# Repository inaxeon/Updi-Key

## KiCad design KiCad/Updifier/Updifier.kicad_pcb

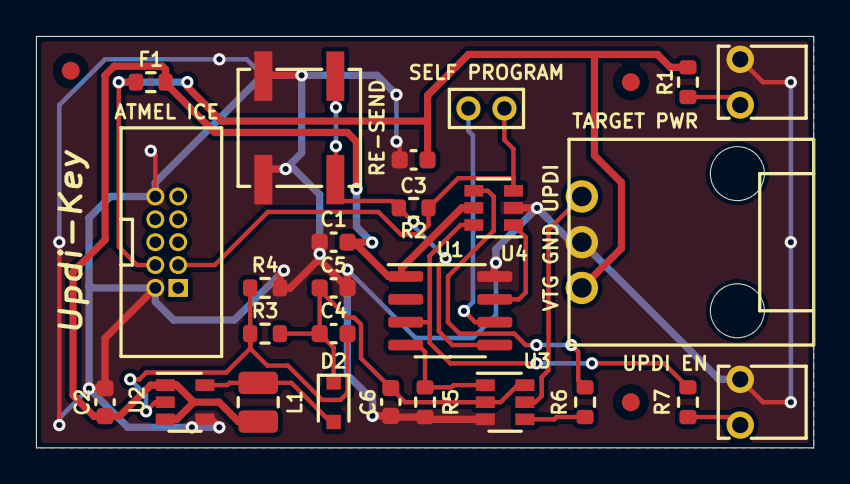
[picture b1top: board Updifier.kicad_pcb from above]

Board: 2 copper layers, 43.2 x 22.9 mm, 29 parts (0 on the bottom side), 17 nets.

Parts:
C1, C6: 0.1µF; C_0603_1608Metric
C2, C3: 10µF; C_0603_1608Metric
C4: 68pF; C_0603_1608Metric
C5: 4.7µF; C_0603_1608Metric
D1: TARGET PWR; WP934AD
D2: PMEG4005CEJX; D_SOD-323F
D3: UPDI EN; WP934AD
F1: 50mA; R_0603_1608Metric
FID1, FID2, FID3: Fiducial; Fiducial_1mm_Mask2mm
J1: ATMEL ICE; SAMTEC_SHF-105-01-X-D-TH
J2: TARGET; SL_3_RA
JP1: JP1; PinHeader_1x02_P2.00mm_Vertical
L1: 47µH; L_1008_2520Metric
R1: 1K; R_0603_1608Metric
R2, R5: 10K; R_0603_1608Metric
R3: 102K 1%; R_0603_1608Metric
R4: 11K 1%; R_0603_1608Metric
R6, R7: 180Ω; R_0603_1608Metric
SW1: RE-SEND; SW_SPST_B3SL-1002P
U1: ATtiny202-SS; SOIC-8_3.9x4.9mm_P1.27mm
U2: NCP1406SNT1G; SOT-23-5
U3: ISL43210IHZ-T; SOT-23-6
U4: SN74LVC1G3157DBVR; SOT-23-6

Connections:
/12V: C4.1, C5.1, C6.1, D2.1, R3.1, U3.2, U3.6
/HVUPDI_TARGET: J2.1, U3.5
/HV_EN: R5.1, U1.4, U3.1
/PROG: JP1.1, U1.6
/UPDI_DAT: U1.7, U4.1
/UPDI_EN: R7.2, U1.3, U4.6
/UPDI_HOST: J1.3, JP1.2, R2.2, U4.3
/UPDI_SENSE: R2.1, SW1.2, U1.5
/VF: C1.1, C2.1, F1.1, L1.1, U1.1, U2.1, U2.3, U4.5
/VTG: C3.1, F1.2, J1.4, J2.3, R1.1
GND: C1.2, C2.2, C3.2, C5.2, C6.2, D1.1, D3.1, J1.2, J1.10, J2.2, R4.2, R5.2, SW1.1, U1.8, U2.4, U3.3, U4.2
unnamed: C4.2, R3.2, R4.1, U2.2
unnamed: D1.2, R1.2
unnamed: D2.2, L1.2, U2.5
unnamed: D3.2, R7.1
unnamed: R6.1, U3.4
unnamed: R6.2, U4.4

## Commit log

2021-06-13 Reverted back to KiCad 5 footprints. Sorted ATMEL ICE pinout mess
2021-06-14 Layout WIP
2021-10-28 Post build fixes
2022-04-21 Release
2022-04-21 Added pre-compile
